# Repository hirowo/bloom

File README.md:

# Bloom
ArduinoNanoブートローダー入り小型電飾モジュール

## 概要
フルカラーLED(WS2812B)をArduinoでコントロールするとき、
Arduinoのサイズが大きく小型のものに組み込みにくい、ということはありませんか？

本モジュールは、ArduinoNanoのブートローダーが組み込まれた小型のモジュールで、
衣装や小道具など、小型のものに組み込むことができます。

もちろん、ArduinoIDEでプログラムの開発を行うことができ、
プログラムを書き込むためのUSBシリアル変換モジュールも搭載しています。

## 特徴
本モジュールは2.4Aまで電流を流せるようにしており、
1個あたり最大50mA程度流すフルカラーLEDであれば、4,50個程度であれば光らせられます。

また、小型化のためおおよそのピンは削ってありますが、
アナログ入力ピン×2とボタンが実装されており、動作のトリガーとして利用できます。

## 使用可能ピン
フルカラーLEDシリアルピン:6  
基板実装ボタン:7  
A3ピン:A3  
A4ピン:A4  

## スペック
サイズ：36×20×5mm  
USBシリアル変換モジュール：FT232RL  

## ArduinoIDEでプログラムを書き換える方へ
ArduinoIDEのツールの設定は、ボード="Arduino Nano"、プロセッサ="ATmega328P"にしてください。

## （自作する人向け）ブートローダー及びヒューズ設定
下記サイトのNano3.1参照。  
https://trac.switch-science.com/wiki/ArduinoFuse#Nano3.1

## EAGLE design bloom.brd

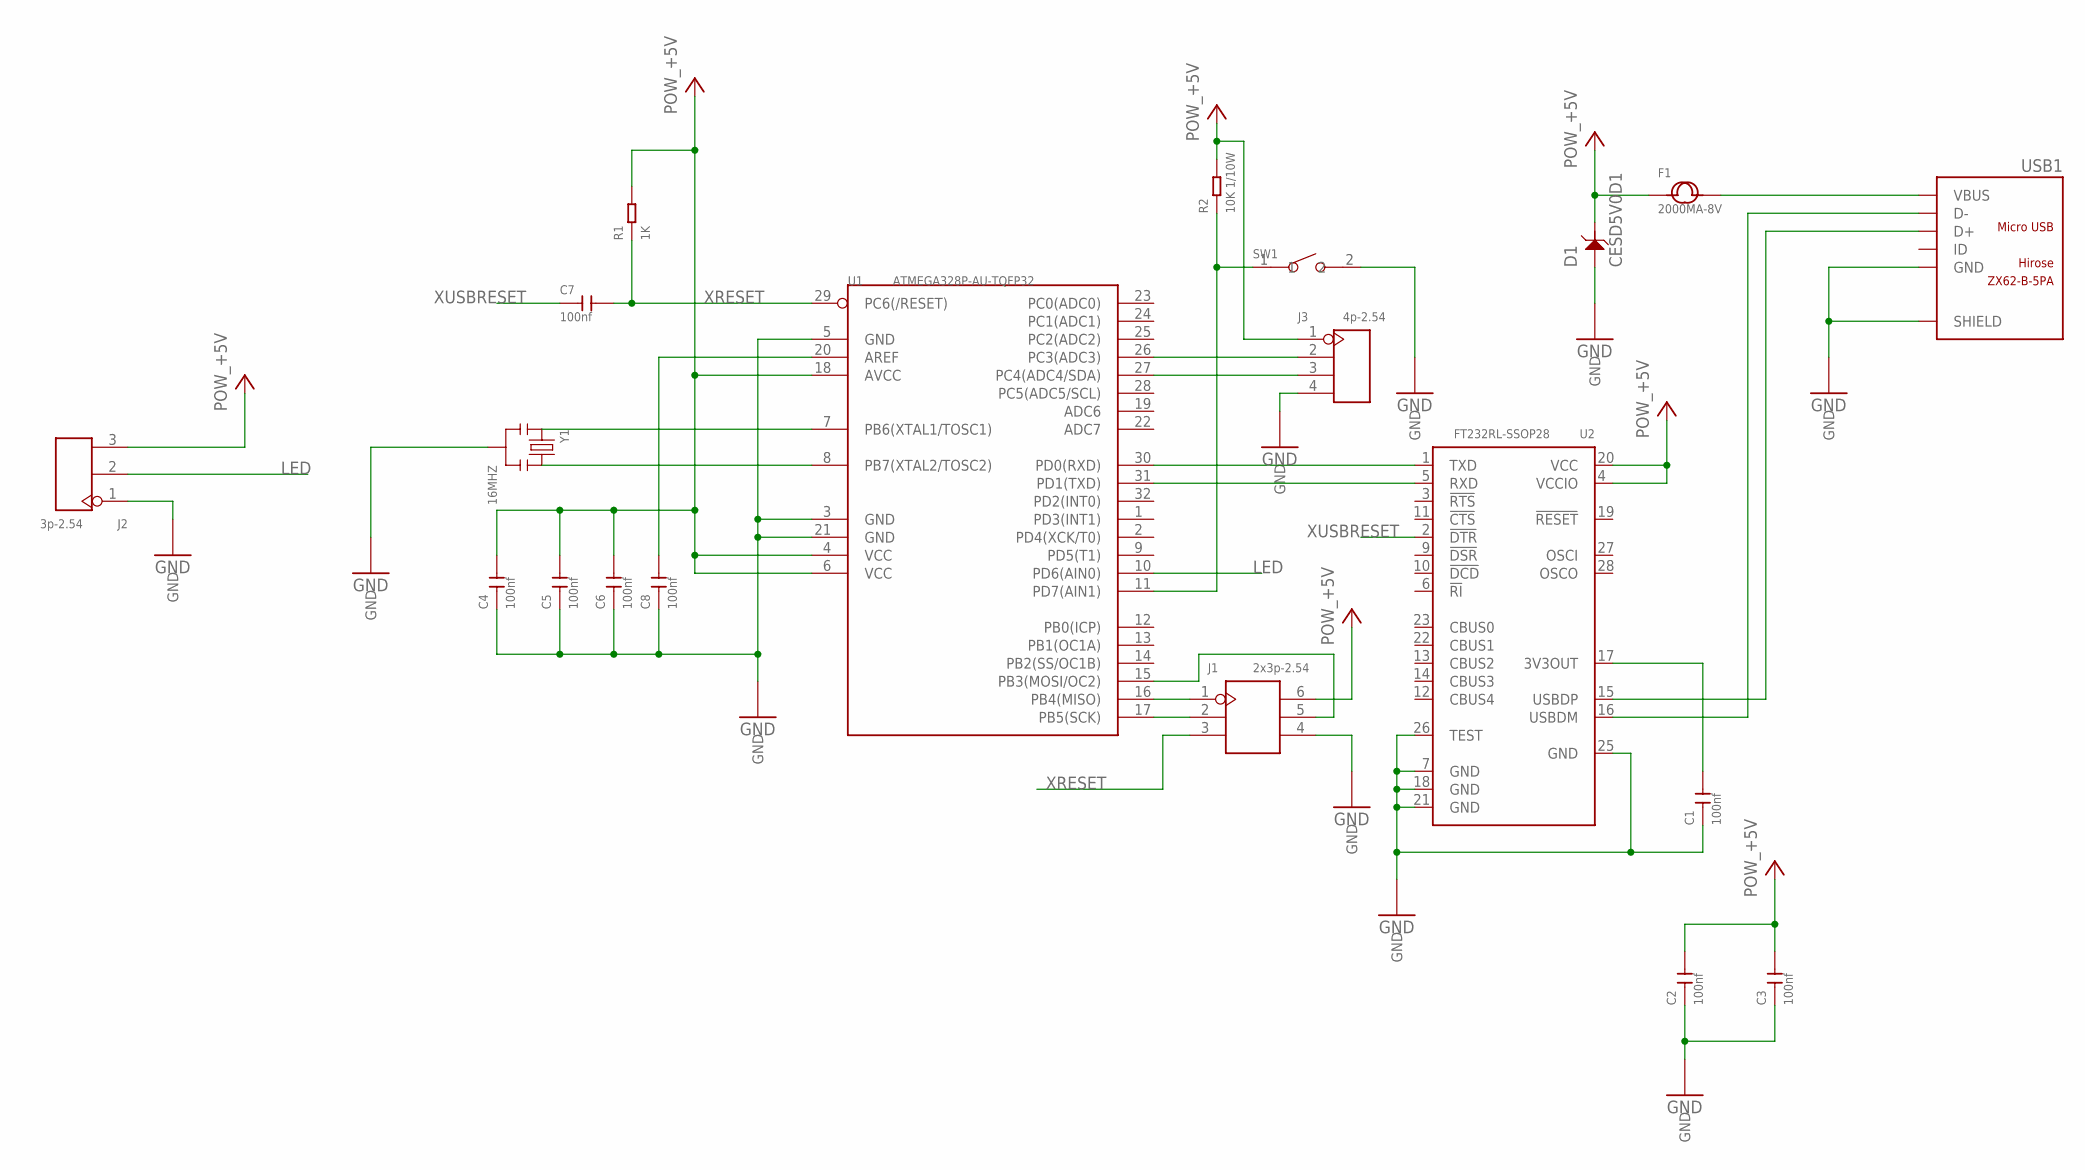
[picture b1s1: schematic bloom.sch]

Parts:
C1, C2, C3, C4, C5, C6, C7, C8: 100nf; C0402
D1: CESD5V0D1; SOD-123
F1: 2000MA-8V; F1210
J1: 2x3p-2.54; H2X3-2.54
J2: 3p-2.54; H3-2.54
J3: 4p-2.54; H4-2.54
R1: 1K; R0603
R2: 10K 1/10W; R0603
SW1: SMD-BUTTON(2P-3.0X2.5X1.2+0.4MM)-B3U-1000P-2P-SMD; SW2-2.6-3.0X2.5X1.2+0.4MM
U1: ATMEGA328P-AU-TQFP32; TQFP32-0.8-7X7MM
U2: FT232RL-SSOP28; SSOP28-0.65-10.2X5.2MM
USB1: ZX62-B-5PA; MICRO-USB5+6P-SMD-0.65-AB
Y1: 16MHZ; X3-SMD-3.6X1.3X0.8MM

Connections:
+5V: C2.2, C3.2, C4.2, C5.2, C6.2, D1.- (2), F1.1, J1.6, J2.3, J3.1, R1.2, R2.2, U1.4 (VCC), U1.6 (VCC), U1.18 (AVCC), U2.4 (VCCIO), U2.20 (VCC)
GND: C1.1, C2.1, C3.1, C4.1, C5.1, C6.1, C8.1, D1.+ (1), J1.4, J2.1, J3.4, SW1.2, U1.3 (GND), U1.5 (GND), U1.21 (GND), U2.7 (GND), U2.18 (GND), U2.21 (GND), U2.25 (GND), U2.26 (TEST), USB1.5 (GND), USB1.P1 (SHIELD), USB1.P2 (SHIELD), USB1.P3 (SHIELD), USB1.P4 (SHIELD), USB1.P5 (SHIELD), USB1.P6 (SHIELD), Y1.2
LED: J2.2, U1.10 (PD6(AIN0))
unnamed: C8.2, U1.20 (AREF)
unnamed: U1.30 (PD0(RXD)), U2.1 (TXD)
unnamed: U1.7 (PB6(XTAL1/TOSC1)), Y1.1
unnamed: U1.31 (PD1(TXD)), U2.5 (RXD)
unnamed: U2.15 (USBDP), USB1.3 (D+)
unnamed: U2.16 (USBDM), USB1.2 (D-)
unnamed: U1.8 (PB7(XTAL2/TOSC2)), Y1.3
unnamed: J1.1, U1.16 (PB4(MISO))
unnamed: J1.2, U1.17 (PB5(SCK))
unnamed: J1.5, U1.15 (PB3(MOSI/OC2))
unnamed: R2.1, SW1.1, U1.11 (PD7(AIN1))
unnamed: C1.2, U2.17 (3V3OUT)
unnamed: J3.2, U1.26 (PC3(ADC3))
unnamed: J3.3, U1.27 (PC4(ADC4/SDA))
VBUS: F1.2, USB1.1 (VBUS)
XRESET: C7.2, J1.3, R1.1, U1.29 (PC6(/RESET))
XUSBRESET: C7.1, U2.2 (!DTR)

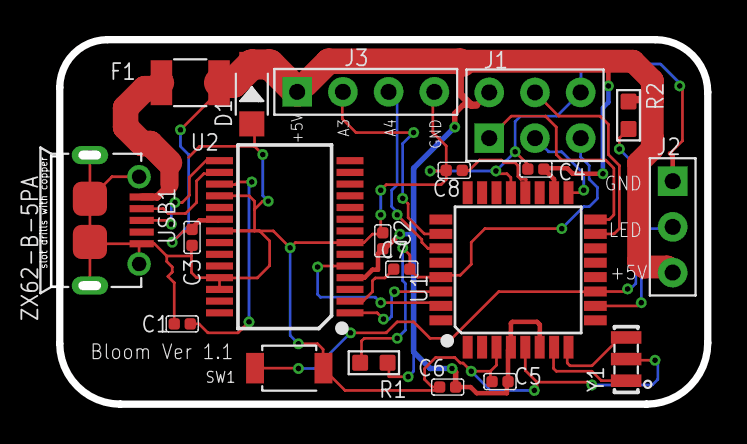
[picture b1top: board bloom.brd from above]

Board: 2 copper layers, 37.0 x 20.1 mm, 20 parts (0 on the bottom side), 20 nets.

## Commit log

2018-10-04 add new file
2018-10-04 Readmeを追加
2018-10-05 Readmeに説明を追加
